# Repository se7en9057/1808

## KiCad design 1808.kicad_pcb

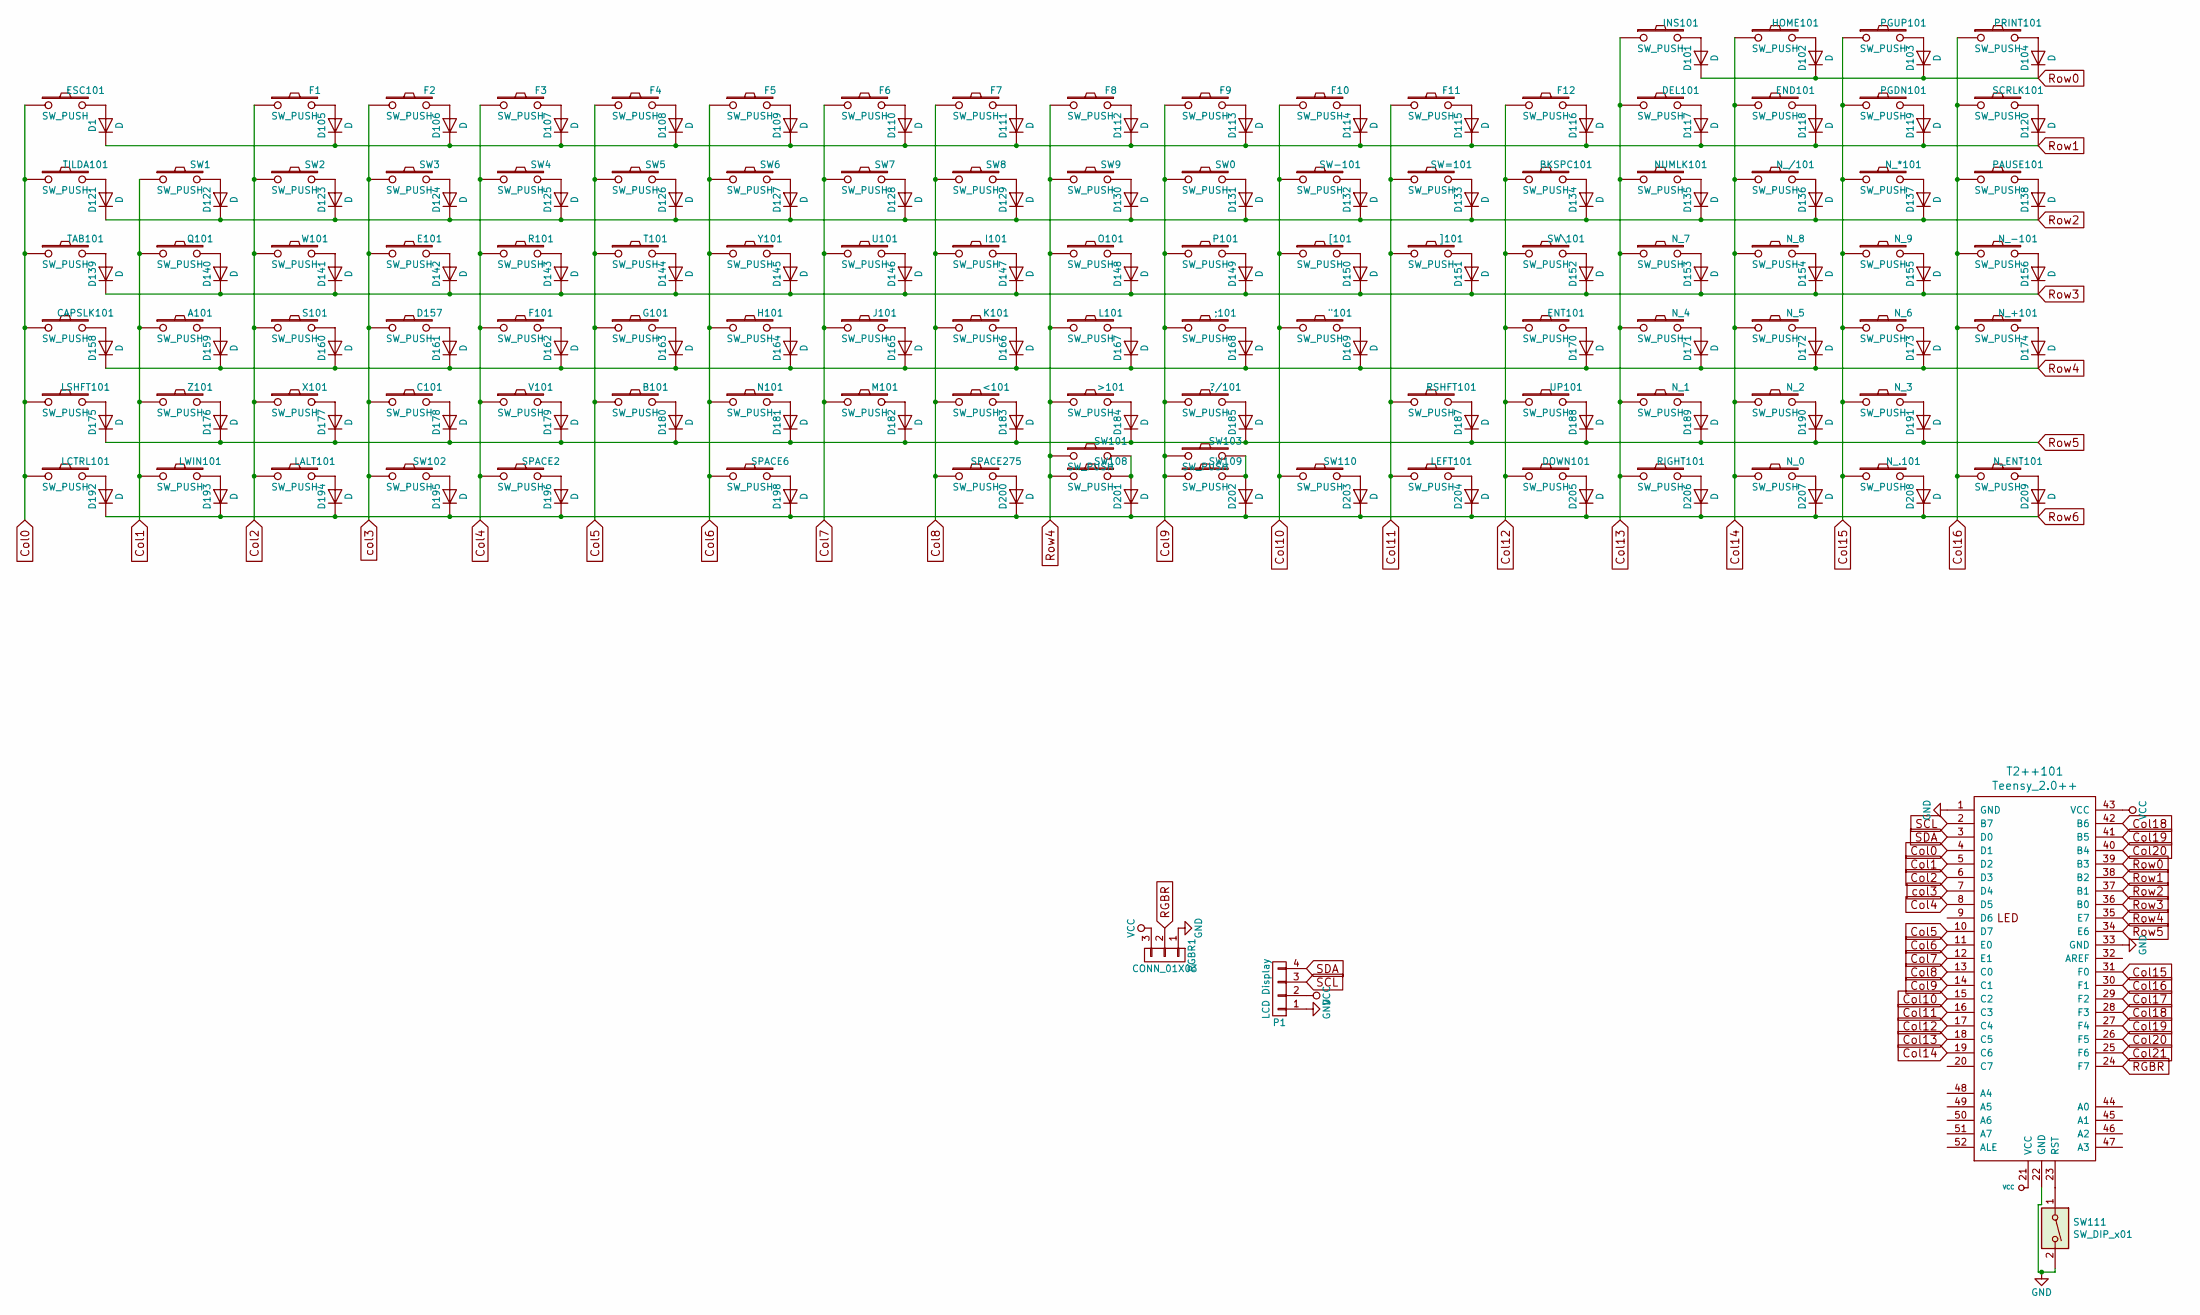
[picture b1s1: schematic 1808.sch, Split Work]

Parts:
"101: SW_PUSH; MXALPS_100_Plated
;101: SW_PUSH; MXALPS_100_Plated
<101: SW_PUSH; MXALPS_100_Plated
>101: SW_PUSH; MXALPS_100_Plated
?/101: SW_PUSH; MXALPS_100_Plated
A101: SW_PUSH; MXALPS_100_Plated
B101: SW_PUSH; MXALPS_100_Plated
BKSPC101: SW_PUSH; MXALPS_200_Plated
C101: SW_PUSH; MXALPS_100_Plated
CAPSLK101: SW_PUSH; MXALPS_175_Plated
D1, D101, D102, D103, D104, D105, D106, D107, D108, D109, D110, D111, D112, D113, D114, D115, D116, D117, D118, D119, D120, D121, D122, D123, D124, D125, D126, D127, D128, D129, D130, D131, D132, D133, D134, D135, D136, D137, D138, D139, D140, D141, D142, D143, D144, D145, D146, D147, D148, D149, D150, D151, D152, D153, D154, D155, D156, D158, D159, D160, D161, D162, D163, D164, D165, D166, D167, D168, D169, D170, D171, D172, D173, D174, D175, D176, D177, D178, D179, D180, D181, D182, D183, D184, D185, D187, D188, D189, D190, D191, D192, D193, D194, D195, D196, D198, D200, D201, D202, D203, D204, D205, D206, D207, D208, D209: D; DIODE_TH_SMD_onesided
D157: SW_PUSH; MXALPS_100_Plated
DEL101: SW_PUSH; MXALPS_100_Plated
DOWN101: SW_PUSH; MXALPS_100_Plated
E101: SW_PUSH; MXALPS_100_Plated
END101: SW_PUSH; MXALPS_100_Plated
ENT101: SW_PUSH; MXALPS_225_Plated
ESC101: SW_PUSH; MXALPS_100_Plated
F1, F2, F3, F4, F5, F6, F7, F8, F9, F10, F11, F12, F101: SW_PUSH; MXALPS_100_Plated
G101: SW_PUSH; MXALPS_100_Plated
H101: SW_PUSH; MXALPS_100_Plated
HOME101: SW_PUSH; MXALPS_100_Plated
I101: SW_PUSH; MXALPS_100_Plated
INS101: SW_PUSH; MXALPS_100_Plated
J101: SW_PUSH; MXALPS_100_Plated
K101: SW_PUSH; MXALPS_100_Plated
L101: SW_PUSH; MXALPS_100_Plated
LALT101: SW_PUSH; MXALPS_125_Plated
LCTRL101: SW_PUSH; MXALPS_125_Plated
LEFT101: SW_PUSH; MXALPS_100_Plated
LSHFT101: SW_PUSH; MXALPS_225_Plated
LWIN101: SW_PUSH; MXALPS_125_Plated
M101: SW_PUSH; MXALPS_100_Plated
N101: SW_PUSH; MXALPS_100_Plated
NUMLK101: SW_PUSH; MXALPS_100_Plated
N_0, N_1, N_2, N_3, N_4, N_5, N_6, N_7, N_8, N_9, N_.101: SW_PUSH; MXALPS_100_Plated
N_*101: SW_PUSH; MXALPS_100_Plated
N_+101: SW_PUSH; MXALPS_100_Plated
N_-101: SW_PUSH; MXALPS_100_Plated
N_/101: SW_PUSH; MXALPS_100_Plated
N_ENT101: SW_PUSH; MXALPS_200_Plated
O101: SW_PUSH; MXALPS_100_Plated
P1: LCD Display; OLED 0.91in display
P101: SW_PUSH; MXALPS_100_Plated
PAUSE101: SW_PUSH; MXALPS_100_Plated
PGDN101: SW_PUSH; MXALPS_100_Plated
PGUP101: SW_PUSH; MXALPS_100_Plated
PRINT101: SW_PUSH; MXALPS_100_Plated
Q101: SW_PUSH; MXALPS_100_Plated
R101: SW_PUSH; MXALPS_100_Plated
RGBR1: CONN_01X03; NetTie-II_SMD
RIGHT101: SW_PUSH; MXALPS_100_Plated
RSHFT101: SW_PUSH; MXALPS_175_Plated
S101: SW_PUSH; MXALPS_100_Plated
SCRLK101: SW_PUSH; MXALPS_100_Plated
SPACE2: SW_PUSH; MXALPS_200_Plated
SPACE6: SW_PUSH; MXALPS_625A_Plated
SPACE275: SW_PUSH; MXALPS_275_Plated
SW0, SW1, SW2, SW3, SW4, SW5, SW6, SW7, SW8, SW9, SW101, SW102, SW103: SW_PUSH; MXALPS_100_Plated
SW108, SW109, SW110: SW_PUSH; MXALPS_125_Plated
SW111: SW_DIP_x01; SW_3.5x6.0_TH
SW-101: SW_PUSH; MXALPS_100_Plated
SW=101: SW_PUSH; MXALPS_100_Plated
SW\101: SW_PUSH; MXALPS_150_Plated
T2++101: Teensy_2.0++; Teensy2.0++
T101: SW_PUSH; MXALPS_100_Plated
TAB101: SW_PUSH; MXALPS_150_Plated
TILDA101: SW_PUSH; MXALPS_100_Plated
U101: SW_PUSH; MXALPS_100_Plated
UP101: SW_PUSH; MXALPS_100_Plated
V101: SW_PUSH; MXALPS_100_Plated
W101: SW_PUSH; MXALPS_100_Plated
X101: SW_PUSH; MXALPS_100_Plated
Y101: SW_PUSH; MXALPS_100_Plated
Z101: SW_PUSH; MXALPS_100_Plated
[101: SW_PUSH; MXALPS_100_Plated
]101: SW_PUSH; MXALPS_100_Plated

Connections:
Col0: CAPSLK101.1, ESC101.1, LCTRL101.1, LSHFT101.1, T2++101.4 (D1), TAB101.1, TILDA101.1
Col1: A101.1, LWIN101.1, Q101.1, SW1.1, T2++101.5 (D2), Z101.1
Col2: F1.1, LALT101.1, S101.1, SW2.1, T2++101.6 (D3), W101.1, X101.1
Col4: F3.1, F101.1, R101.1, SPACE2.1, SW4.1, T2++101.8 (D5), V101.1
Col5: B101.1, F4.1, G101.1, SW5.1, T2++101.10 (D7), T101.1
Col6: F5.1, H101.1, N101.1, SPACE6.1, SW6.1, T2++101.11 (E0), Y101.1
Col7: F6.1, J101.1, M101.1, SW7.1, T2++101.12 (E1), U101.1
Col8: <101.1, F7.1, I101.1, K101.1, SPACE275.1, SW8.1, T2++101.13 (C0)
Col9: ;101.1, ?/101.1, F9.1, P101.1, SW0.1, SW103.1, SW109.1, T2++101.14 (C1)
Col10: "101.1, F10.1, SW110.1, SW-101.1, T2++101.15 (C2), [101.1
Col11: F11.1, LEFT101.1, RSHFT101.1, SW=101.1, T2++101.16 (C3), ]101.1
Col12: BKSPC101.1, DOWN101.1, ENT101.1, F12.1, SW\101.1, T2++101.17 (C4), UP101.1
Col13: DEL101.1, INS101.1, NUMLK101.1, N_1.1, N_4.1, N_7.1, RIGHT101.1, T2++101.18 (C5)
Col14: END101.1, HOME101.1, N_0.1, N_2.1, N_5.1, N_8.1, N_/101.1, T2++101.19 (C6)
Col15: N_3.1, N_6.1, N_9.1, N_*101.1, N_.101.1, PGDN101.1, PGUP101.1, T2++101.31 (F0)
Col16: N_+101.1, N_-101.1, N_ENT101.1, PAUSE101.1, PRINT101.1, SCRLK101.1, T2++101.30 (F1)
Col18: T2++101.28 (F3), T2++101.42 (B6)
Col19: T2++101.27 (F4), T2++101.41 (B5)
Col20: T2++101.26 (F5), T2++101.40 (B4)
GND: P1.1, RGBR1.1, SW111.2, T2++101.1 (GND), T2++101.22 (GND), T2++101.33 (GND)
unnamed: "101.2, D169.2 (A)
unnamed: ;101.2, D168.2 (A)
unnamed: <101.2, D183.2 (A)
unnamed: >101.2, D184.2 (A)
unnamed: ?/101.2, D185.2 (A)
unnamed: A101.2, D159.2 (A)
unnamed: B101.2, D180.2 (A)
unnamed: BKSPC101.2, D134.2 (A)
unnamed: C101.2, D178.2 (A)
unnamed: CAPSLK101.2, D158.2 (A)
unnamed: D1.2 (A), ESC101.2
unnamed: D101.2 (A), INS101.2
unnamed: D102.2 (A), HOME101.2
unnamed: D103.2 (A), PGUP101.2
unnamed: D104.2 (A), PRINT101.2
unnamed: D105.2 (A), F1.2
unnamed: D106.2 (A), F2.2
unnamed: D107.2 (A), F3.2
unnamed: D108.2 (A), F4.2
unnamed: D109.2 (A), F5.2
unnamed: D110.2 (A), F6.2
unnamed: D111.2 (A), F7.2
unnamed: D112.2 (A), F8.2
unnamed: D113.2 (A), F9.2
unnamed: D114.2 (A), F10.2
unnamed: D115.2 (A), F11.2
unnamed: D116.2 (A), F12.2
unnamed: D117.2 (A), DEL101.2
unnamed: D118.2 (A), END101.2
unnamed: D119.2 (A), PGDN101.2
unnamed: D120.2 (A), SCRLK101.2
unnamed: D121.2 (A), TILDA101.2
unnamed: D122.2 (A), SW1.2
unnamed: D123.2 (A), SW2.2
unnamed: D124.2 (A), SW3.2
unnamed: D125.2 (A), SW4.2
unnamed: D126.2 (A), SW5.2
unnamed: D127.2 (A), SW6.2
unnamed: D128.2 (A), SW7.2
unnamed: D129.2 (A), SW8.2
unnamed: D130.2 (A), SW9.2
unnamed: D131.2 (A), SW0.2
unnamed: D132.2 (A), SW-101.2
unnamed: D133.2 (A), SW=101.2
unnamed: D135.2 (A), NUMLK101.2
unnamed: D136.2 (A), N_/101.2
unnamed: D137.2 (A), N_*101.2
unnamed: D138.2 (A), PAUSE101.2
unnamed: D139.2 (A), TAB101.2
unnamed: D140.2 (A), Q101.2
unnamed: D141.2 (A), W101.2
unnamed: D142.2 (A), E101.2
unnamed: D143.2 (A), R101.2
unnamed: D144.2 (A), T101.2
unnamed: D145.2 (A), Y101.2
unnamed: D146.2 (A), U101.2
unnamed: D147.2 (A), I101.2
unnamed: D148.2 (A), O101.2
unnamed: D149.2 (A), P101.2
unnamed: D150.2 (A), [101.2
unnamed: D151.2 (A), ]101.2
unnamed: D152.2 (A), SW\101.2
unnamed: D153.2 (A), N_7.2
unnamed: D154.2 (A), N_8.2
unnamed: D155.2 (A), N_9.2
unnamed: D156.2 (A), N_-101.2
unnamed: D157.2, D161.2 (A)
unnamed: D160.2 (A), S101.2
unnamed: D162.2 (A), F101.2
unnamed: D163.2 (A), G101.2
unnamed: D164.2 (A), H101.2
unnamed: D165.2 (A), J101.2
unnamed: D166.2 (A), K101.2
unnamed: D167.2 (A), L101.2
unnamed: D170.2 (A), ENT101.2
unnamed: D171.2 (A), N_4.2
unnamed: D172.2 (A), N_5.2
unnamed: D173.2 (A), N_6.2
unnamed: D174.2 (A), N_+101.2
unnamed: D175.2 (A), LSHFT101.2
unnamed: D176.2 (A), Z101.2
unnamed: D177.2 (A), X101.2
unnamed: D179.2 (A), V101.2
unnamed: D181.2 (A), N101.2
unnamed: D182.2 (A), M101.2
unnamed: D187.2 (A), RSHFT101.2
unnamed: D188.2 (A), UP101.2
unnamed: D189.2 (A), N_1.2
unnamed: D190.2 (A), N_2.2
unnamed: D191.2 (A), N_3.2
unnamed: D192.2 (A), LCTRL101.2
unnamed: D193.2 (A), LWIN101.2
unnamed: D194.2 (A), LALT101.2
unnamed: D195.2 (A), SW102.2
unnamed: D196.2 (A), SPACE2.2
unnamed: D198.2 (A), SPACE6.2
unnamed: D200.2 (A), SPACE275.2
unnamed: D201.2 (A), SW101.2, SW108.2
unnamed: D202.2 (A), SW103.2, SW109.2
unnamed: D203.2 (A), SW110.2
unnamed: D204.2 (A), LEFT101.2
unnamed: D205.2 (A), DOWN101.2
unnamed: D206.2 (A), RIGHT101.2
unnamed: D207.2 (A), N_0.2
unnamed: D208.2 (A), N_.101.2
unnamed: D209.2 (A), N_ENT101.2
unnamed: RGBR1.2, T2++101.24 (F7)
unnamed: SW111.1, T2++101.23 (RST)
Row0: D101.1 (K), D102.1 (K), D103.1 (K), D104.1 (K), T2++101.39 (B3)
Row1: D1.1 (K), D105.1 (K), D106.1 (K), D107.1 (K), D108.1 (K), D109.1 (K), D110.1 (K), D111.1 (K), D112.1 (K), D113.1 (K), D114.1 (K), D115.1 (K), D116.1 (K), D117.1 (K), D118.1 (K), D119.1 (K), D120.1 (K), T2++101.38 (B2)
Row2: D121.1 (K), D122.1 (K), D123.1 (K), D124.1 (K), D125.1 (K), D126.1 (K), D127.1 (K), D128.1 (K), D129.1 (K), D130.1 (K), D131.1 (K), D132.1 (K), D133.1 (K), D134.1 (K), D135.1 (K), D136.1 (K), D137.1 (K), D138.1 (K), T2++101.37 (B1)
Row3: D139.1 (K), D140.1 (K), D141.1 (K), D142.1 (K), D143.1 (K), D144.1 (K), D145.1 (K), D146.1 (K), D147.1 (K), D148.1 (K), D149.1 (K), D150.1 (K), D151.1 (K), D152.1 (K), D153.1 (K), D154.1 (K), D155.1 (K), D156.1 (K), T2++101.36 (B0)
Row4: >101.1, D158.1 (K), D159.1 (K), D160.1 (K), D161.1 (K), D162.1 (K), D163.1 (K), D164.1 (K), D165.1 (K), D166.1 (K), D167.1 (K), D168.1 (K), D169.1 (K), D170.1 (K), D171.1 (K), D172.1 (K), D173.1 (K), D174.1 (K), F8.1, L101.1, O101.1, SW9.1, SW101.1, SW108.1, T2++101.35 (E7)
Row5: D175.1 (K), D176.1 (K), D177.1 (K), D178.1 (K), D179.1 (K), D180.1 (K), D181.1 (K), D182.1 (K), D183.1 (K), D184.1 (K), D185.1 (K), D187.1 (K), D188.1 (K), D189.1 (K), D190.1 (K), D191.1 (K), T2++101.34 (E6)
Row6: D192.1 (K), D193.1 (K), D194.1 (K), D195.1 (K), D196.1 (K), D198.1 (K), D200.1 (K), D201.1 (K), D202.1 (K), D203.1 (K), D204.1 (K), D205.1 (K), D206.1 (K), D207.1 (K), D208.1 (K), D209.1 (K)
SCL: P1.3, T2++101.2 (B7)
SDA: P1.4, T2++101.3 (D0)
VCC: P1.2, RGBR1.3, T2++101.21 (VCC), T2++101.43 (VCC)
col3: C101.1, D157.1, E101.1, F2.1, SW3.1, SW102.1, T2++101.7 (D4)

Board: 2 copper layers, 236 parts (1 on the bottom side), 138 nets, no tracks yet.

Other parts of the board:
HOLE_M3, HOLE_M3#2, HOLE_M3#3, HOLE_M3#4, HOLE_M3#5, HOLE_M3#6, HOLE_M3#7, HOLE_M3#8, HOLE_M3#9, HOLE_M3#10, HOLE_M3#11, HOLE_M3#12, HOLE_M3#13, HOLE_M3#14, HOLE_M3#15, HOLE_M3#16, HOLE_M3#17, HOLE_M3#18, HOLE_M3#19: VAL**; HOLE_M3
